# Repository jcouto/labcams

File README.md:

MMM
                                           MMMMMM
    MMM:               .MMMM             MMMM MMMMMMMM
    MMM:               .MMMM            MMMMM MMMMMMMM      
    MMM:               .MMMM             MMMM  MMMMMM        MM 
    MMM:  :MMMMMMMMM.  .MMMMOMMMMMM       MN     MMM      MMMMM 
    MMM:  :M     MMMM  .MMMMM?+MMMMM    MMMMMMMMMMMMMMM7MMMMMMM  
    MMM:         OMMM  .MMMM    MMMM    MMMMMMMMMMMMMMMMMMMMMMM 
    MMM:  .MMMMMMMMMM  .MMMM    ?MMM    MMMMMMMMMMMMMMMMMMMMMMM 
    MMM:  MMMM  .8MMM  .MMMM    ZMMM    MMMMMMMMMMMMMMMMMMMMMMM 
    MMM:  MMM=...8MMM  .MMMM    MMMM    MMMMMMMMMMMMMMM.MMMMMMM  
    MMM:  MMMMMMMMMMM  .MMMMMMMMMMM                        MMMM 
    MMM:   MMMMM 8MMM  .MMMM:MMMMZ                            M 

         MMMMMMN  =MMMMMMMM     MMMM.MMMM$ .+MMMM      MMMMMMM: 
       MMMMMMMMM  +MMMMMMMMM$   MMMMMMMMMMMMMMMMMM   MMMMMMMMM8 
      MMMM               MMMM   MMMM   MMMM    MMM+  MMM8       
      MMMZ          OMMMMMMMM   MMMM   NMMM    MMM?  MMMMMMM$   
      MMMI        MMMMM  MMMM   MMMM   NMMM    MMM?   ZMMMMMMMM 
      MMMM       7MMM    MMMM   MMMM   NMMM    MMM?        MMMM 
       MMMMD+7MM  MMMN   MMMM   MMMM   NMMM    MMM?  MM$:.7MMMM   
        MMMMMMMM  ZMMMMMOMMMM   MMMM   NMMM    MMM?  MMMMMMMM+  
                          https://bitbucket.org/jpcouto/labcams   

Multicamera control and acquisition.

This aims to facilitate video acquisition and automation of experimens, uses separate processes to record and store data. Interfaces with other computers via UDP or ZeroMQ for automating experiments. Uses hardware and FFMPEG to compress in real-time. 

## Instalation from pip (recommended but not the latest version):

``pip install labcams`` or add the ``--no-deps`` flag to install no dependencies.

Install camera [drivers](./camera_instructions.md):

## Usage:

Open a terminal and type ``labcams -h`` for help.

The first time you run ``labcams`` it will create a folder in the user home directory where the default preference file is stored.

### Command line options:

|       |  command     | description |
|-------|--------------|-------------|
| ``-w``| ``--wait``   | start with software trigger OFF |
| ``-t``| ``--triggered`` |  start with hardware trigger ON |
| ``-c X Y`` | ``--cam-select X Y``     |  start only some cameras ``-c 0 1`` |
| ``-d PATH`` | ``--make-config PATH``  |  create a configuration file |
| | ``--no-server`` | do not start the ZMQ nor the UDP server |

## Configuration files:

Configuration files ensure you always use the same parameters during your experiments.

The configuration files are simple ``json`` files. There are 2 parts to the files.

1. ``cams`` - **camera descriptions** - each camera has a section to store acquisition and recording parameters.

Available camera drivers:

 * `PCO` - install pco.sdk
 * `AVT` - install Vimba SDK and pymba
 * `QImaging` 
 * `pointgrey` - FLIR cameras - install Spinnaker
 * `openCV` - webcams and so on

For calcium or voltage imaging with the PCO (or another) camera use the arduino code in the ``duino`` folder and [instructions](./camera_instructions.md).

Each camera has its own parameters, there are some parameters that are common to all:

* `recorder` - the type of recorder `tiff` `ffmpeg` `opencv` `binary`
 * `haccel` - `nvidia` or `intel` for use with ffmpeg for compression.

**NOTE:** You need to get ffmpeg compiled with `NVENC` from [here](https://developer.nvidia.com/ffmpeg) - precompiled versions are avaliable - `conda install ffmpeg` works. Make sure to have python recognize it in the path (using for example `which ffmpeg` to confirm from git bash)/

**NOTE** To use `intel` acceleration you need to download the [mediaSDK](https://software.intel.com/content/www/us/en/develop/tools/media-sdk.html).

2. **general parameters** to control the remote communication ports and general gui or recording parameters.

 * `recorder_frames_per_file` number of frames per file
 * `recorder_path` the path of the recorder, how to handle substitutions - needs more info.

3. Aditional parameters:

 * 'CamStimTrigger' - controls the arduino camera trigger, see the duino examples folder.

### UDP and ZMQ:

``labcams`` can listen for UDP or ZMQ commands.

To configure use the command ``"server":"udp"`` in the end of the config file.

The port can be configured with ``"server_port":9999``

The UDP commands are:

 * Set the experiment name ``expname=EXPERIMENT_NAME``
 * Software trigger the cameras ``softtrigger=1`` (multiple cameras are not in sync)
 * Hardware trigger mode and save ``trigger=1``
 * Start/stop saving ``manualsave=1``
 * Add a message to the log ``log=MESSAGE``
 * Quit ``quit``

### Supported cameras -  [see instructions here](./camera_instructions.md):

 * PCO cameras (only windows)
 * PointGrey cameras (via PySpin)
 * Basler cameras (via pypylon)
 * Allied Vision Technologies (via pymba - updating to the latest)
 * QImaging cameras via the legacy driver (only windows)
 * Ximea cameras

### Features:

 * Separates viewer, camera control/acquisition and file writer in different processes.
 * Data from camera acquisition process placed on a cue.
 * Display options: background subtraction; histogram equalization; pupil tracking via the [ mptracker ](https://bitbucket.org/jpcouto/mptracker).	
 * Multiple buffers on Allied vision technologies cameras allows high speed data acquisition.
 * Online compression using ffmpeg (supports hardware acceleration)

## Instalation on Ubuntu 20.04

``sudo apt install python3-matplotlib ipython3 python3-opencv python3-pyqt5 python3-tqdm python3-pip python3-pyqtgraph python3-serial python3-zmq python3-natsort python3-pandas emacs git ssh ffmpeg``

``pip3 install labcams`` - this may end up in ``$HOME/.local/bin`` so add the following to the end of the ``.bashrc`` file: ``export PATH=$PATH:$HOME/.local/bin``

## Instalation - from git:

**Note:** On windows get the [ git bash terminal ](https://git-scm.com/downloads). I had issues running from cmd.exe when installed with conda.

1. Get [ anaconda ](https://conda.io/anaconda.html). Add conda to system PATH when asked. Open a terminal (use git bash if on windows) and type ``conda init bash``.
2. Clone the repository: ``git clone git@bitbucket.org:jpcouto/labcams.git``
3. Go into the cloned ``cd labcams`` folder.
4. Install the required packages, use e.g. ``pip install -r requirements.txt`` or conda install... 
5. Install ``labcams`` with ``python setup.py develop``
6. Follow the [camera specific instalation](./camera_instructions.md) and instructions for syncronization. Each camera must have a section in the ``~/labcams/default.json`` file that is created the first time you try to run the software with the command ``labcams`` from the terminal. Use a text editor to add the correct options. There are examples in the examples folder.
7. Install ffmpeg with anaconda: ``conda install -c conda-forge ffmpeg`` 

You can run ``labcams`` from the command terminal. 

**Please drop me a line for feedback and let the world know if you use this.**

Joao Couto - jpcouto@gmail.com

May 2017

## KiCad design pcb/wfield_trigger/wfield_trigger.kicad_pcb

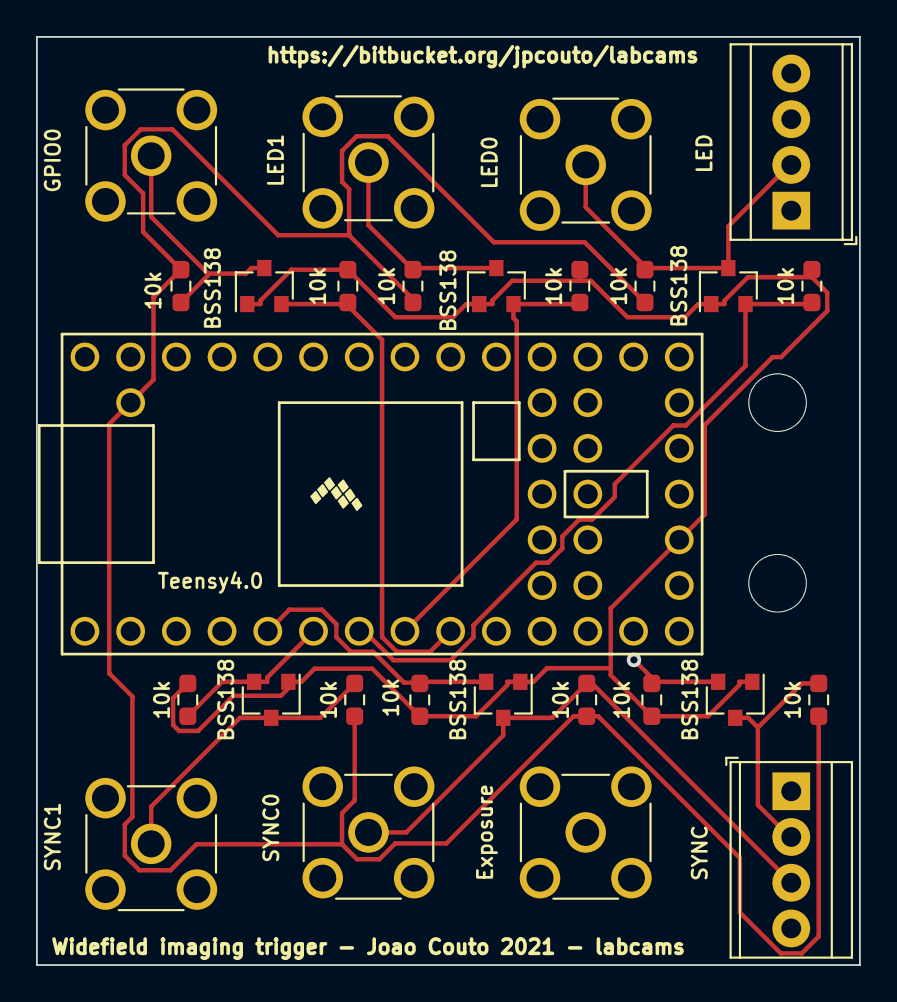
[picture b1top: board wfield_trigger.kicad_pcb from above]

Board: 4 copper layers, 45.7 x 51.6 mm, 29 parts (0 on the bottom side), 15 nets.

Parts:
J1: SYNC; TerminalBlock_TE_282834-4_1x04_P2.54mm_Horizontal
J2: LED; TerminalBlock_TE_282834-4_1x04_P2.54mm_Horizontal
J3: LED1; SMA_Molex_73251-2200_Horizontal
J4: Exposure; SMA_Molex_73251-2200_Horizontal
J5: SYNC1; SMA_Molex_73251-2200_Horizontal
J6: SYNC0; SMA_Molex_73251-2200_Horizontal
J7: LED0; SMA_Molex_73251-2200_Horizontal
J8: GPIO0; SMA_Molex_73251-2200_Horizontal
Q1, Q2, Q3, Q4, Q5, Q6: BSS138; SOT-23
R1, R2, R3, R4, R5, R6, R7, R8, R9, R10, R11, R12: 10k; R_0603_1608Metric_Pad0.98x0.95mm_HandSolder
U1: Teensy4.0; Teensy40
mount1, mount2: MountingHole_3.2mm_M3

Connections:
+3V3: Q1.1, Q2.1, Q3.1, Q4.1, Q5.1, Q6.1, R2.1, R4.1, R6.1, R8.1, R10.1, R12.1, U1.16
+5V: R1.2, R3.2, R5.2, R7.2, R9.2, R11.2, U1.34
GND: J1.1, J2.1, J3.2, J4.2, J5.2, J6.2, J7.2, J8.2, U1.1, U1.17, U1.32
cam_trigger: Q1.2, R2.2, U1.4
cam_trigger_out: J1.2, J4.1, Q1.3, R1.1
gpio0: Q6.2, R12.2, U1.9
gpio0_out: J2.4, J8.1, Q6.3, R11.1
led0: Q4.2, R8.2, U1.7
led0_out: J2.2, J7.1, Q4.3, R7.1
led1: Q5.2, R10.2, U1.8
led1_out: J2.3, J3.1, Q5.3, R9.1
sync0: Q2.2, R4.2, U1.5
sync0_out: J1.3, J6.1, Q2.3, R3.1
sync1: Q3.2, R6.2, U1.6
sync1_out: J1.4, J5.1, Q3.3, R5.1

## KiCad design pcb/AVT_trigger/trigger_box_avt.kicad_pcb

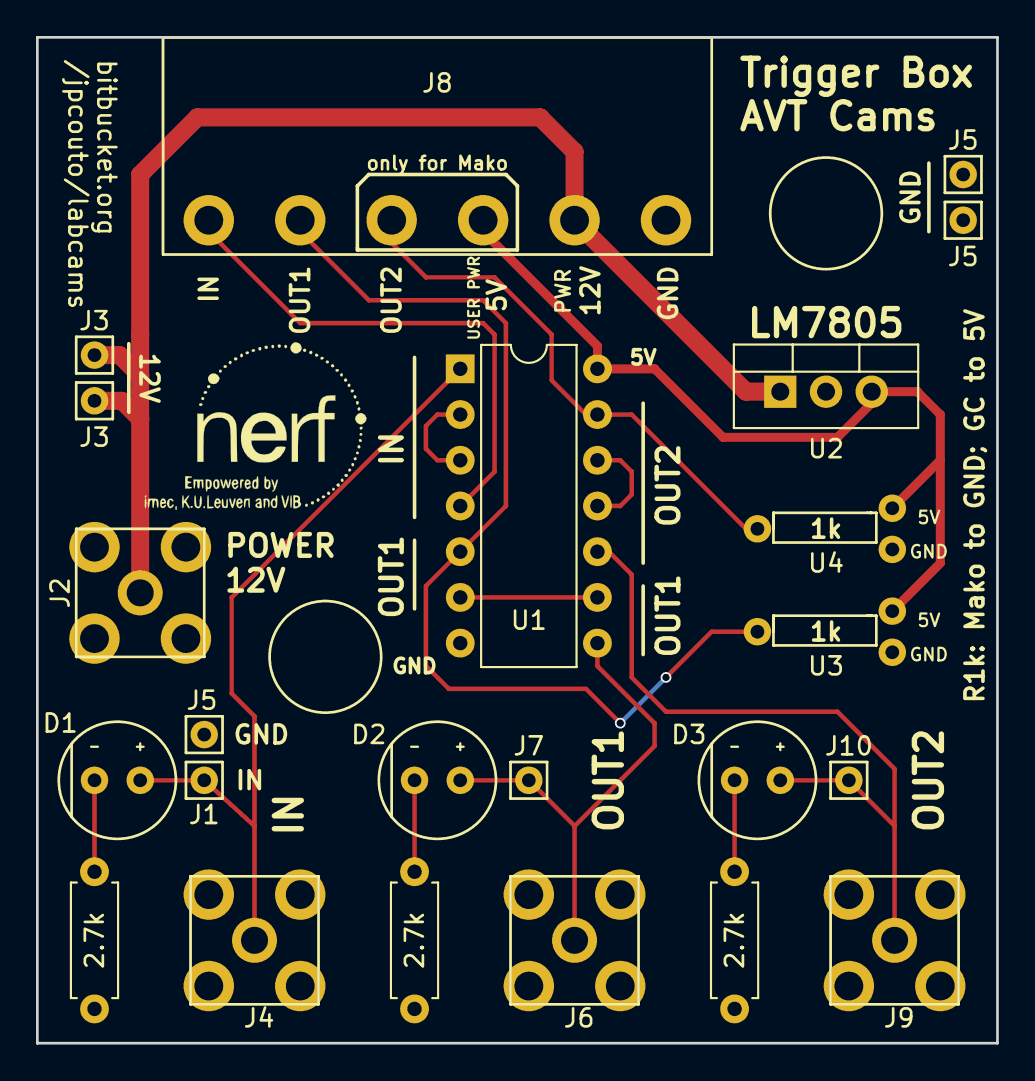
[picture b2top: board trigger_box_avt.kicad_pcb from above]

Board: 2 copper layers, 53.3 x 55.9 mm, 23 parts (0 on the bottom side), 15 nets.

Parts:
2.7k, 2.7k#2, 2.7k#3: R; R_Axial_DIN0207_L6.3mm_D2.5mm_P7.62mm_Horizontal
D1, D2, D3: LED; LED_THT_standard
J1, J3, J3#2, J5, J5#2, J5#3, J7, J10: Conn_01x01; conn_01x01
J2, J4, J6, J9: Conn_Coaxial; SMA_female
J8: Conn_01x06; Conn_1x6
U1: 74hct14; DIP-14_W7.62mm
U2: LM7805_TO220; TO-220-3_Vertical
U3, U4: Resistor_choice; Resistor_THT_choice

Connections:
+5V: J8.4, U1.14, U2.3, U3.2, U4.2
+12V: J2.1, J3.1, J3#2.1, J8.5, U2.1
GND: 2.7k.2, 2.7k#2.2, 2.7k#3.2, J1.1, J2.2, J4.2, J5.1, J5#2.1, J6.2, J8.6, J9.2, U1.7, U2.2, U3.3, U4.3
unnamed: 2.7k.1, D1.1
unnamed: 2.7k#2.1, D2.1
unnamed: 2.7k#3.1, D3.1
unnamed: D1.2, J4.1, J5#3.1, U1.1
unnamed: D2.2, J6.1, J7.1, U1.8
unnamed: D3.2, J9.1, J10.1, U1.10
unnamed: J8.1, U1.4
unnamed: J8.2, U1.5, U3.1
unnamed: J8.3, U1.13, U4.1
unnamed: U1.2, U1.3
unnamed: U1.6, U1.9
unnamed: U1.11, U1.12

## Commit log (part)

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2019-02-12 Lap triggered average added to gui analysis options.
2019-02-13 Trim number of reference frames for baseline in binLaps
2019-02-14 cv threads set in writer for use with mptracker.
2019-02-15 Add to the image when in eye tracker mode.
2019-02-16 TiffWriter empties queue. Default points for mptracker.
2019-02-19 Can specify cameras based on device_id. Example configuration files.
2019-02-19 Set mptracker widgets closable.
2019-02-21 analysis mode options.
2019-05-27 Set fixed size to 600 on widgets. Using pyqtgraph autorange.
2019-05-30 Updated for mptracker roi selection.
2019-05-31 Added realtime display regions of interest during acquisition.
2019-05-31 Set cam widgets resizable. Set fixed aspect ratio on view.
2019-06-02 Slider on context menu to control n subtracted frames.
2019-06-02 Checkbox on menu for equalize histogram.
2019-06-03 Default number of buffers for AVT cams increased.
2019-06-28 Removed invert X from defaults. Nsubtract with fixed number of zeros.
2019-09-16 Started adjusting to add a save toggle feature.
2019-09-18 Separated avt and qimaging cams. Imports conditional on selected driver on gui.
2019-09-19 Reshape buffers before broadcast.
2019-09-19 Squeeze img when initializing mptracker.
2019-09-21 resize after equalize hist
2019-10-10 avt and pco using the new interface.
2019-10-11 OpenCV cam on new interface.
2019-10-11 fixed lastframeid because of new interface.
2019-10-11 Cleaning up menus; QActionSlider and QActionCheckBox added.
2019-10-14 Opencv cam start stop
2019-10-14 Separator on menu. Eye tracker widget to checkbox.
2019-10-15 PCO set exposure from widget
2019-10-22 Widgets can control avt and pco with multiple parameters.
2019-10-23 Print campulses and num frames.
2019-10-23 Space before number of frames on no save text.
2019-10-23 Ximea binning support.
2019-10-25 Ximea disable LED lights.
2019-10-31 Interpolate on first and last frame when sync is messed up.
2019-12-19 UDP server control, can control some aspects of the GUI controller through the server.
2020-01-19 Removed eye tracker from TiffWriter and moved most of the logic out.
2020-01-20 Added roi selection to PointGrey cameras. [Warning: labcams expects valid rois.]
2020-01-21 Hide loop duration text.
2020-02-05 Pass frame rate to writer when ffmpeg or opencv. Use intel hardware on ffmpeg. Close writer from the cam queue.
2020-02-05 Pixels format and hardware triggers for pointgrey.
2020-02-06 Moved queue logic to genericcam
2020-02-06 Settings for global quality and look ahead.
2020-02-11 Handle no recorder parameters and empty queue.
2020-02-13 QFileDialog to change he refresh rate of the GUI. Using skvideo because ffmpeg does not write nb_frames.
2020-02-13 Added requirements.txt
2020-02-16 Moved server to earlier on the init. Exposed software trigger to the CLI.
2020-02-17 Simplified inheritance for the FFmpegCamWriter
2020-02-18 More options on docked tabs. Logo on readme and description.
2020-02-18 Readme includes more features.
2020-02-24 removed feature list AVT
2020-02-25 Auto exposure ON for opencv cams when rate is 0
2020-03-07 pco updated to get frameid from frame first bytes.
2020-03-08 Arduino code for driving LEDs with camera exposure pulse. PCO updated to stop acquiring on software trigger.
2020-03-09 Save LED info to the log when using with PCO.
2020-03-10 Fast preset for nvenc; specify cq 19
2020-03-12 No trackerToggle on mptracker. Nan mean of the roi. Disable sharpness auto on pointgrey cameras.
2020-03-16 Close files even when stop was not called.
2020-03-21 Added parse_log_comments example to get trials start and end info
2020-05-24 Prevent crash when failing to set frame rate on pgcamerage
2020-06-15 BinaryCamWriter for recording on acquisition when the queue is the bottleneck (e.g. PCO at 500Hz).
2020-06-23 Trial info on pco. Save button closes the log file.
2020-06-26 Start stim teensy in the armed reset state
2020-06-27 Pass datafolder to the writer. Stop writing while savwaitng for triggers
2020-06-27 PCO clears the buffer when stopped with a software trigger.
2020-06-27 PointGrey camera default to no ExposureAuto off, SharpnessAuto off and set line 3 to output if hardware_trigger out_line3
2020-06-27 Moved first channel to green when displaying 2 channels.
2020-06-28 Datatype writen to the filename of binary files.
2020-06-28 Added some instructions to the readme. Made compress not mandatory on the parameter.
2020-06-28 Removed legacy ffmpeg. Camera exposure of triggered is timed.
2020-06-29 Bold logo.
2020-06-29 Logo indent.
2020-06-29 Table for listing commands.
2020-06-29 List on the config description.
2020-07-01 Can start pco without teensy
2020-07-07 Added way to probe capabilities and modes from the teensy.
2020-07-07 PCO takes binning from camera if None. Set combo stim mode to nothing.
2020-07-07 Added pointgrey example.
2020-07-09 Changed sync log order. Instructions when camera driver fails load.
2020-07-09 Teensy resets sync time before changing the sync_count.
2020-07-09 Experimental saturation mode to show regions that are saturating in red.
2020-07-09 binary_noqueue closes and uses queue for logging only.
2020-07-13 ROI clears on display change.
2020-07-14 Added example of 1p sanity plots.
2020-07-17 Opencv example json.
2020-08-11 Added gated example.
2020-08-15 Gated example to micros
2020-08-18 Example to check sync between PCO and teensy.
2020-08-20 Draft of camera instructions.
2020-08-20 camera_instructions.md edited, images not rendering
2020-08-20 UDP instructions bullets
2020-08-30 Added acquire and snapshot buttons. Edit for experiment name does not need enter pressed. Fixed height for the controller. Controller is not central widget.
2020-09-04 Clipping tiff compression to 9. Compress lossless if recording uint16 with single channel data on ffmpeg.
2020-09-06 Mptracker fix after display multiple channels. Using Manager.list instead of Array to transfer images.
2020-09-10 memlist instead of buf fixed.
2020-09-10 Test stop spinaker trigger exposure.
2020-09-10 Can use lowecase names in the camera, SaveMethod is still accepted. Readme updated.
2020-09-10 qimaging to use the buffer the same as others
2020-09-29 Read bits
2020-11-19 Added default sleep time for the recorder.
2020-11-25 Changed order of cameras so the master is the last if ordered on the file. Delay before triggering master.
2020-11-29 Removed trigger functions and other old visual stim processing stuff that are in wfield now.
2020-11-29 Early draft of the configuration file example.
2020-12-03 Channels passed to the recorders. Enter on edit saves filename. Recorders init method sets nchannels and frame_rate. Frame rate defined for all cam drivers.
2020-12-11 Added license file.
2020-12-14 RoiWidget can take multiple existing roi.
2020-12-14 ROI widget working with multichannel images.
2020-12-16 Instructions for ubuntu.
2020-12-18 Pathformat for noqueue.
2020-12-18 Message when the recorder is not implemented in cams noqueue
2020-12-29 Set the line2 of the pointgrey cam to input.
2020-12-29 added user folder to pco driver. changed order of the drop menu to match on the ino. try on timestamp from pco.
2021-01-25 Draft of the widget for choosing cam properties.
2021-02-26 Auto-downsample true and don't crash when can't set PCO on CamLink
2021-03-18 changed default compression values (higher default - smaller files)
2021-03-19 Added support for basler cameras.
2021-06-02 Added comments to the examples
2021-06-02 Updated instructions and readme.
2021-06-02 Smaller size for teensy box.
2021-08-03 PointGrey can specify different trigger lines.
2021-09-11 3 cam trigger for blackfly
2021-09-20 Chameleon and blackfly working with triggering.
2021-09-29 Change the frame rate enable before trying to disable auto for chamaeleon cameras.
2021-11-02 Firefly cameras also don t have set auto.
2021-11-05 Added try before setting trigger overlap on pointgrey.
2021-12-04 Read teensylog even when there are no syncs
2021-12-05 Get the number of channels from the duino when running with CamStimTrigger.
2021-12-08 Added preset to ffmpeg options.
2022-02-02 Draft of the nidaq recorder.
2022-02-03 Widget to visualize analog channels. Save analog in int16. Events to nidaq to behave like a camera.
2022-02-05 ibl example connection for nidaq
2022-02-06 5M default bitrate for the nvidia encoder. NVIDIA HQ settings with nvenc.
2022-02-10 Colors reference for eye tracker using out of object.
2022-03-03 Released labcams 0.4
2022-04-03 PCO now works with shared memory, saving and excitation control still needs work.
2022-04-05 Removed acquisition stim trigger from PCO so the excitation control module can be used with any camera.
2022-04-05 Set the number of virtual channels for the BinaryWriter when there is excitation trigger,
2022-04-05 Control events loaded by the widget
2022-04-06 Implemented lock, perhaps not useful. Changed floor division to mod when assigning buffer.
2022-04-06 Adapted examples to the new json format.
2022-04-12 Fixed ROI in pointgrey Camera
2022-04-14 NIDAQ working with camera object.
2022-04-14 Update virtual channels when writing excitation_trigger.
2022-05-31 Added shared date and more path options for names
2022-06-02 Can run pointgrey without hardware trigger and frame_rate. Can add plugins updated at every refresh. Seerver does not start by default
2022-06-09 Take snapshots using virtual channels.
2022-07-07 Parentesis missing on virtual channels snapshot.
2022-07-15 Save snapshots and load references from UDP/ZMQ. Cleaned up UDP/ZMQ handling.
2022-07-27 ascontiguousarray cast on nidaq recorder. PCO sizes where flipped.
2022-07-29 Don't try to set line 2 and 3 in BlackFly cameras.
2022-07-29 Removed value from toggle_reference call.
2022-07-30 Set auto buffer handling and cleans buffers before stopping.
2022-07-31 Use many manual buffers for PCO. Try to read from all buffers before closing acquisition.
2022-08-01 Use max buffer count if smaller than the requested.
2022-08-02 Changed compress to compression in ffmpeg options of the examples.
2022-08-03 PyPi release server 0.6 with multi-buffer handling on pointgrey cameras and nidaq recording capability.
2022-08-11 Corrected number of digital channels in BinaryDAQWriter
2022-08-14 Snapshots work on color images. And on virtual channels.
2022-08-17 Upgraded to version 0.6.5 and pushed to pip. Python >=3.8 in the requirements so it works with python 3.8.0.
2022-09-08 Added pvcam draft.
2022-09-08 PVCam with forced parameters.
2022-09-11 Don't downsample when applying the reference.
2022-09-11 Deleted some commented code on pointgrey
2022-09-29 Initialize the queues max size. Drop frames if the queue grows forever.
2022-10-30 set context in application, outside cams.py
2022-10-31 Force method spawn for all contexts by starting on cams.py with a try catch. This was needed in some ubuntu systems.
2023-01-18 Deeplabcut live to detect licking in the plugin.
2023-06-01 require opencv-python-headless instead of opencv-python
2023-07-12 Bumped version and removed install_requires. Changed requirement to headless opencv
2023-07-16 requirements are back.
2023-07-16 pco cleans buffers
2023-07-18 Bumped to 0.7.0 for pip release
2023-07-18 Enable recording with the nidaq usb-6001 (that does not have counters).
2023-07-22 PCO in FIFO mode. Example with sync.
2023-07-25 basename and foldername added to the io recorder to build filepaths.
2023-12-05 Tifffile save typo.
2023-12-06 Try to stop the pco recording because the cam sometimes fails.
2023-12-06 Switched writer flag to writer_event.
2023-12-06 Removed stream not started messages in pointgrey
2024-02-17 Widefield trigger can disable violet light.
2025-04-15 Added a warning for the CM3 cameras when not supporting the line.
2025-04-16 Added FLIR test at 30Hz with PCO and nidaq.
2025-04-21 Formatting and updated AVT driver to use VmbPy.
